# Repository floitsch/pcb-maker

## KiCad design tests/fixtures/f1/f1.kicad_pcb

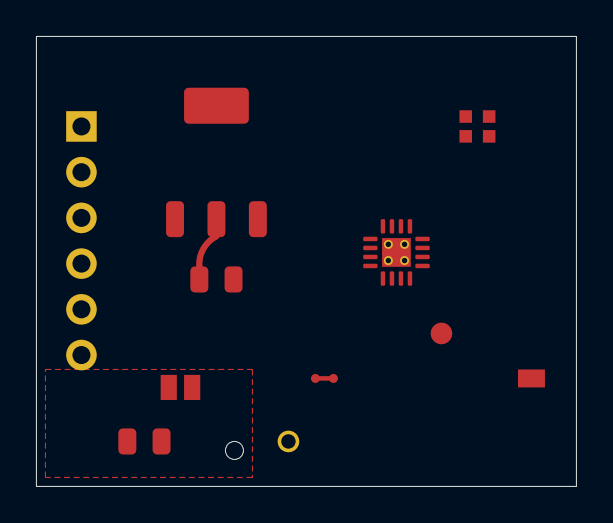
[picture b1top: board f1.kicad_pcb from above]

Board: 2 copper layers, 30.0 x 25.0 mm, 13 parts (0 on the bottom side), 10 nets.

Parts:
C1: 1u; C_0805
D1: WS2812B-2020; LED_WS2812B-2020
H1: Slot; MountingHole_Slot_1.2x2.2mm
H2: Pin; MountingHole_MaskOnly
J1: Conn_01x06; PinHeader_1x06_P2.54mm
J2: Probe; EdgePad_Stacked
JP1: Jumper; SolderJumper-2_Bridged
NT1: NetTie; NetTie-2_SMD_Pad0.5mm
R1: 10k; R_0805
TP1: 5V; TestPoint_Padstack
TP2: GND; TestPoint_Pad_D1.2mm
U1: MCU; QFN-16-1EP_3x3mm_P0.5mm_ThermalVias
U2: LDO_3V3; SOT-223-3_TabPin2

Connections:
14: J1.3, JP1.1, JP1.2, U1.5
+3V3: C1.1, U1.1, U2.2
+5V: D1.1, J1.1, R1.1, TP1.1, U2.3
AGND: NT1.2, U1.9
DIN: D1.4, U1.4
DOUT: D1.2, J1.4
GND: C1.2, D1.3, J1.2, NT1.1, R1.2, TP2.1, U1.2, U1.17, U2.1
PA: J1.5, U1.10
PB: J1.6, U1.12
SIG: J2.1, U1.8
